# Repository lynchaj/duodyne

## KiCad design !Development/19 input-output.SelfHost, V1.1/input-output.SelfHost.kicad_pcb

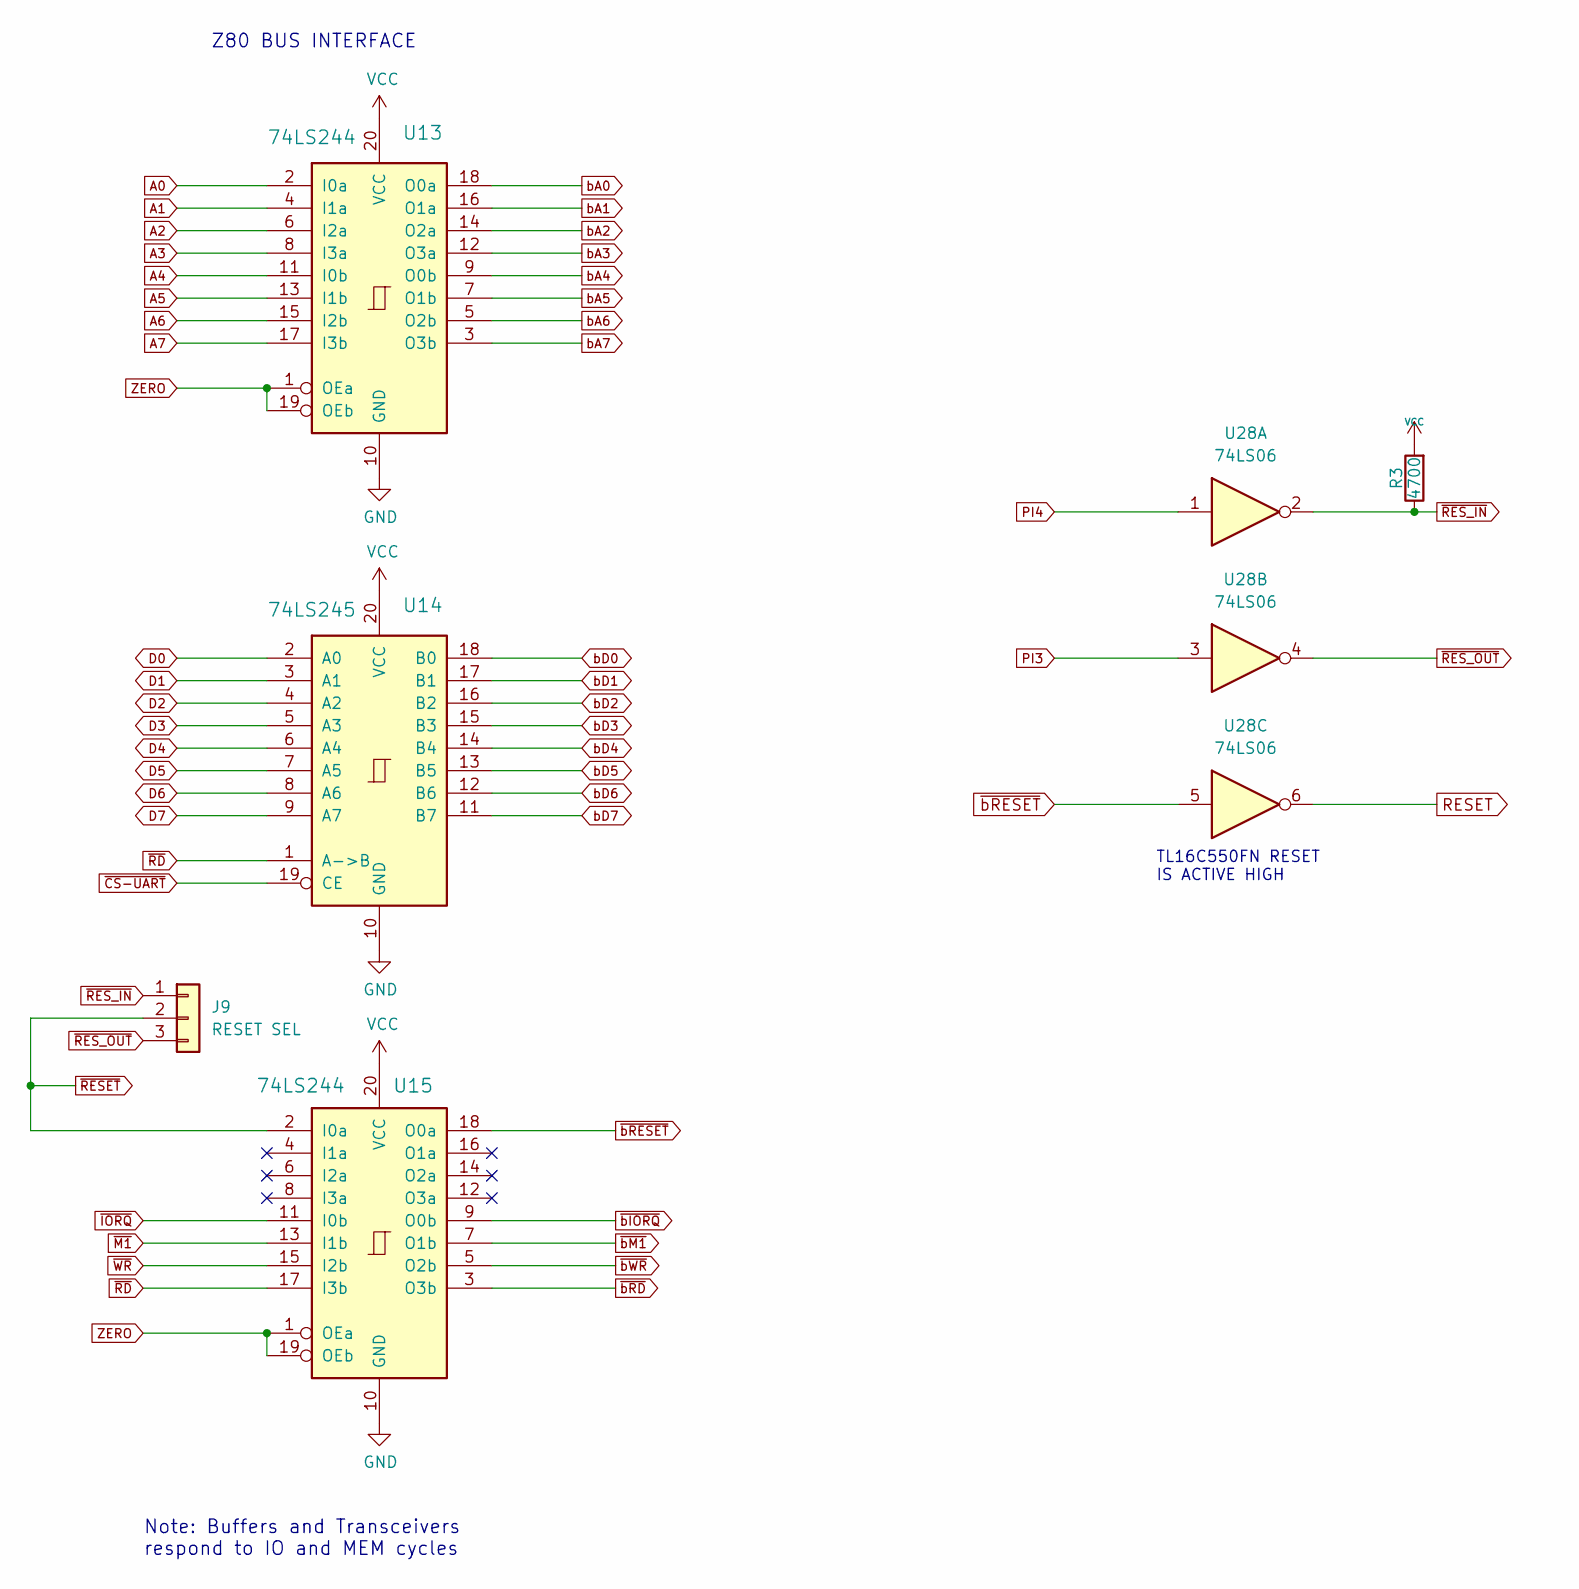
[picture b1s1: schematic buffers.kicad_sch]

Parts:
J9: RESET SEL; PinHeader_1x03_P2.54mm_Vertical
R3: 4700; R_Axial_DIN0207_L6.3mm_D2.5mm_P7.62mm_Horizontal
U13, U15: 74LS244; DIP-20_W7.62mm_Socket
U14: 74LS245; DIP-20_W7.62mm_Socket
U28: 74LS06

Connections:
A0: U13.2 (I0a); also elsewhere on the board
A1: U13.4 (I1a); also elsewhere on the board
A2: U13.6 (I2a); also elsewhere on the board
A5: U13.13 (I1b); also elsewhere on the board
A6: U13.15 (I2b); also elsewhere on the board
A7: U13.17 (I3b); also elsewhere on the board
D0: U14.2 (A0); also elsewhere on the board
D1: U14.3 (A1); also elsewhere on the board
D2: U14.4 (A2); also elsewhere on the board
D3: U14.5 (A3); also elsewhere on the board
D4: U14.6 (A4); also elsewhere on the board
D5: U14.7 (A5); also elsewhere on the board
D6: U14.8 (A6); also elsewhere on the board
D7: U14.9 (A7); also elsewhere on the board
PI3: U28.3; also elsewhere on the board
PI4: U28.1; also elsewhere on the board
RESET: U28.6; also elsewhere on the board
ZERO: U13.1 (OEa), U13.19 (OEb), U15.1 (OEa), U15.19 (OEb); also elsewhere on the board
bA0: U13.18 (O0a); also elsewhere on the board
bA1: U13.16 (O1a); also elsewhere on the board
bA2: U13.14 (O2a); also elsewhere on the board
bA4: U13.9 (O0b); also elsewhere on the board
bA5: U13.7 (O1b); also elsewhere on the board
bA6: U13.5 (O2b); also elsewhere on the board
bA7: U13.3 (O3b); also elsewhere on the board
bD0: U14.18 (B0); also elsewhere on the board
bD1: U14.17 (B1); also elsewhere on the board
bD2: U14.16 (B2); also elsewhere on the board
bD3: U14.15 (B3); also elsewhere on the board
bD4: U14.14 (B4); also elsewhere on the board
bD5: U14.13 (B5); also elsewhere on the board
bD6: U14.12 (B6); also elsewhere on the board
bD7: U14.11 (B7); also elsewhere on the board
~IORQ: U15.11 (I0b); also elsewhere on the board
~M1: U15.13 (I1b); also elsewhere on the board
~RD: U14.1 (A->B), U15.17 (I3b); also elsewhere on the board
~RESET: J9.2, U15.2 (I0a); also elsewhere on the board
~RES_IN: J9.1, R3.1, U28.2; also elsewhere on the board
~RES_OUT: J9.3, U28.4; also elsewhere on the board
~WR: U15.15 (I2b); also elsewhere on the board
~bIORQ: U15.9 (O0b); also elsewhere on the board
~bM1: U15.7 (O1b); also elsewhere on the board
~bRD: U15.3 (O3b); also elsewhere on the board
~bRESET: U15.18 (O0a), U28.5; also elsewhere on the board
~bWR: U15.5 (O2b); also elsewhere on the board

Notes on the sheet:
TL16C550FN RESET IS ACTIVE HIGH
Z80 BUS INTERFACE
Note: Buffers and Transceivers respond to IO and MEM cycles

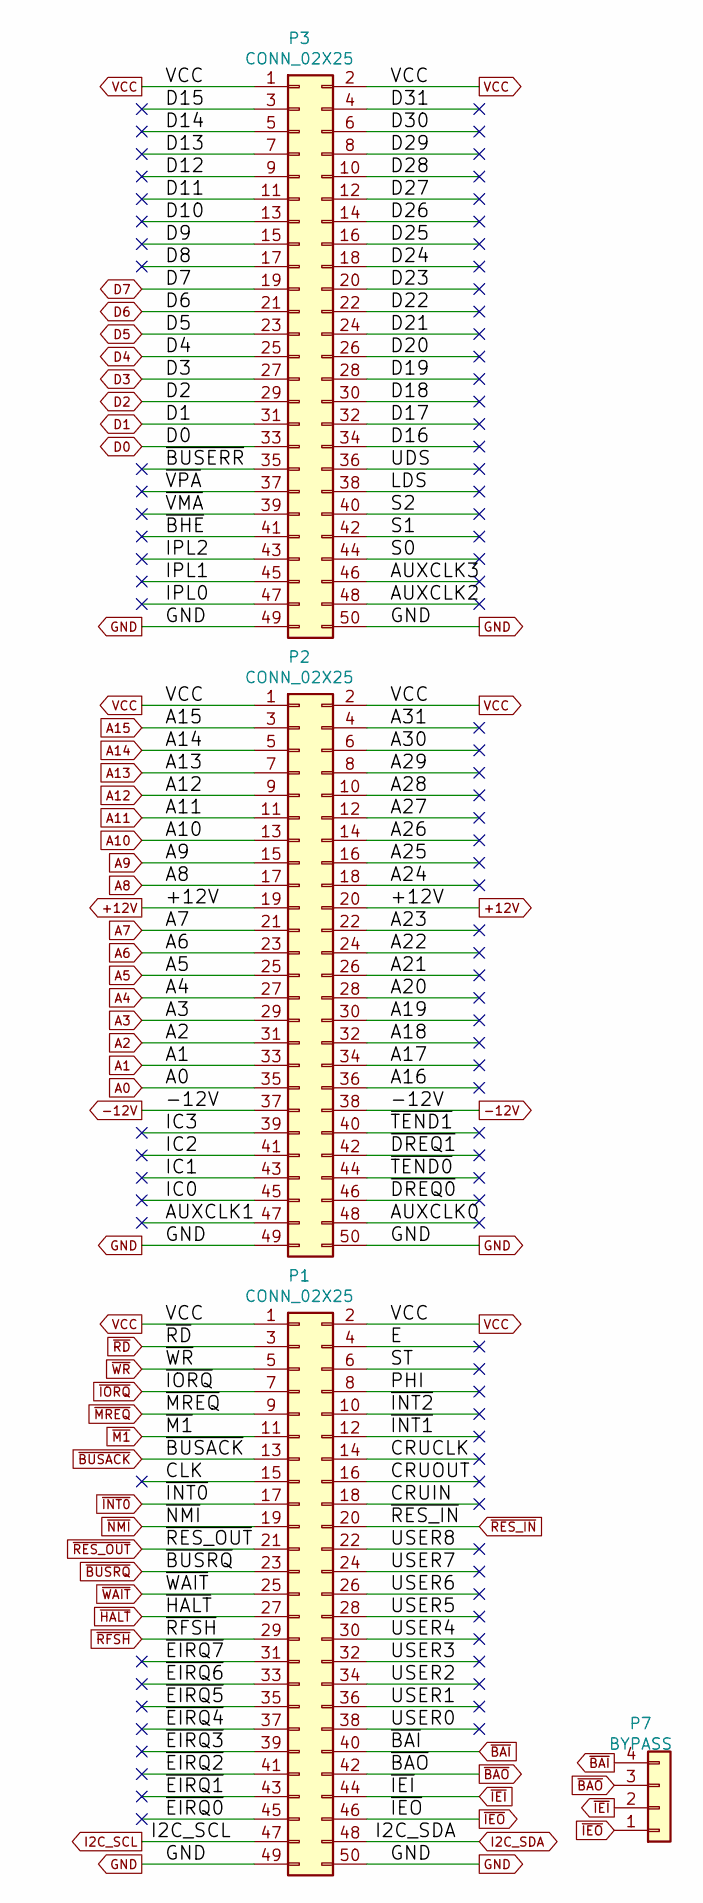
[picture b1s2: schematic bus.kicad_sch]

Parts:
P1, P2, P3: CONN_02X25; IDC-Header_2x25_P2.54mm_Horizontal
P7: BYPASS; PinHeader_1x04_P2.54mm_Vertical

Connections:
+12V: P2.19, P2.20
-12V: P2.37, P2.38
/bus/A16: P2.36
/bus/A17: P2.34
/bus/A18: P2.32
/bus/A19: P2.30
/bus/A20: P2.28
/bus/A21: P2.26
/bus/A22: P2.24
/bus/A23: P2.22
/bus/A24: P2.18
/bus/A25: P2.16
/bus/A26: P2.14
/bus/A27: P2.12
/bus/A28: P2.10
/bus/A29: P2.8
/bus/A30: P2.6
/bus/A31: P2.4
/bus/AUXCLK0: P2.48
/bus/AUXCLK1: P2.47
/bus/AUXCLK2: P3.48
/bus/AUXCLK3: P3.46
/bus/CLK: P1.15
/bus/CRUCLK: P1.14
/bus/CRUIN: P1.18
/bus/CRUOUT: P1.16
/bus/D8: P3.17
/bus/D9: P3.15
/bus/D10: P3.13
/bus/D11: P3.11
/bus/D12: P3.9
/bus/D13: P3.7
/bus/D14: P3.5
/bus/D15: P3.3
/bus/D16: P3.34
/bus/D17: P3.32
/bus/D18: P3.30
/bus/D19: P3.28
/bus/D20: P3.26
/bus/D21: P3.24
/bus/D22: P3.22
/bus/D23: P3.20
/bus/D24: P3.18
/bus/D25: P3.16
/bus/D26: P3.14
/bus/D27: P3.12
/bus/D28: P3.10
/bus/D29: P3.8
/bus/D30: P3.6
/bus/D31: P3.4
/bus/E: P1.4
/bus/IC0: P2.45
/bus/IC1: P2.43
/bus/IC2: P2.41
/bus/IC3: P2.39
/bus/IPL0: P3.47
/bus/IPL1: P3.45
/bus/IPL2: P3.43
/bus/LDS: P3.38
/bus/PHI: P1.8
/bus/S0: P3.44
/bus/S1: P3.42
/bus/S2: P3.40
/bus/ST: P1.6
/bus/UDS: P3.36
/bus/USER0: P1.38
/bus/USER1: P1.36
/bus/USER2: P1.34
/bus/USER3: P1.32
/bus/USER4: P1.30
/bus/USER5: P1.28
/bus/USER6: P1.26
/bus/USER7: P1.24
/bus/USER8: P1.22
/bus/~BHE: P3.41
/bus/~BUSERR: P3.35
/bus/~DREQ0: P2.46
/bus/~DREQ1: P2.42
/bus/~EIRQ0: P1.45
/bus/~EIRQ1: P1.43
/bus/~EIRQ2: P1.41
/bus/~EIRQ3: P1.39
/bus/~EIRQ4: P1.37
/bus/~EIRQ5: P1.35
/bus/~EIRQ6: P1.33
/bus/~EIRQ7: P1.31
/bus/~INT1: P1.12
/bus/~INT2: P1.10
/bus/~TEND0: P2.44
/bus/~TEND1: P2.40
/bus/~VMA: P3.39
/bus/~VPA: P3.37
A0: P2.35; also elsewhere on the board
A1: P2.33; also elsewhere on the board
A2: P2.31; also elsewhere on the board
A5: P2.25; also elsewhere on the board
A6: P2.23; also elsewhere on the board
A7: P2.21; also elsewhere on the board
A8: P2.17; also elsewhere on the board
A9: P2.15; also elsewhere on the board
A10: P2.13; also elsewhere on the board
A11: P2.11; also elsewhere on the board
A12: P2.9; also elsewhere on the board
A13: P2.7; also elsewhere on the board
A14: P2.5; also elsewhere on the board
A15: P2.3; also elsewhere on the board
D0: P3.33; also elsewhere on the board
D1: P3.31; also elsewhere on the board
D2: P3.29; also elsewhere on the board
D3: P3.27; also elsewhere on the board
D4: P3.25; also elsewhere on the board
D5: P3.23; also elsewhere on the board
D6: P3.21; also elsewhere on the board
D7: P3.19; also elsewhere on the board
I2C_SCL: P1.47; also elsewhere on the board
I2C_SDA: P1.48; also elsewhere on the board
~BAI: P1.40, P7.4
~BAO: P1.42, P7.3
~BUSACK: P1.13; also elsewhere on the board
~HALT: P1.27; also elsewhere on the board
~IEO: P1.46, P7.1; also elsewhere on the board
~INT0: P1.17; also elsewhere on the board
~IORQ: P1.7; also elsewhere on the board
~M1: P1.11; also elsewhere on the board
~MREQ: P1.9; also elsewhere on the board
~NMI: P1.19; also elsewhere on the board
~RD: P1.3; also elsewhere on the board
~RES_IN: P1.20; also elsewhere on the board
~RES_OUT: P1.21; also elsewhere on the board
~RFSH: P1.29; also elsewhere on the board
~WAIT: P1.25; also elsewhere on the board
~WR: P1.5; also elsewhere on the board

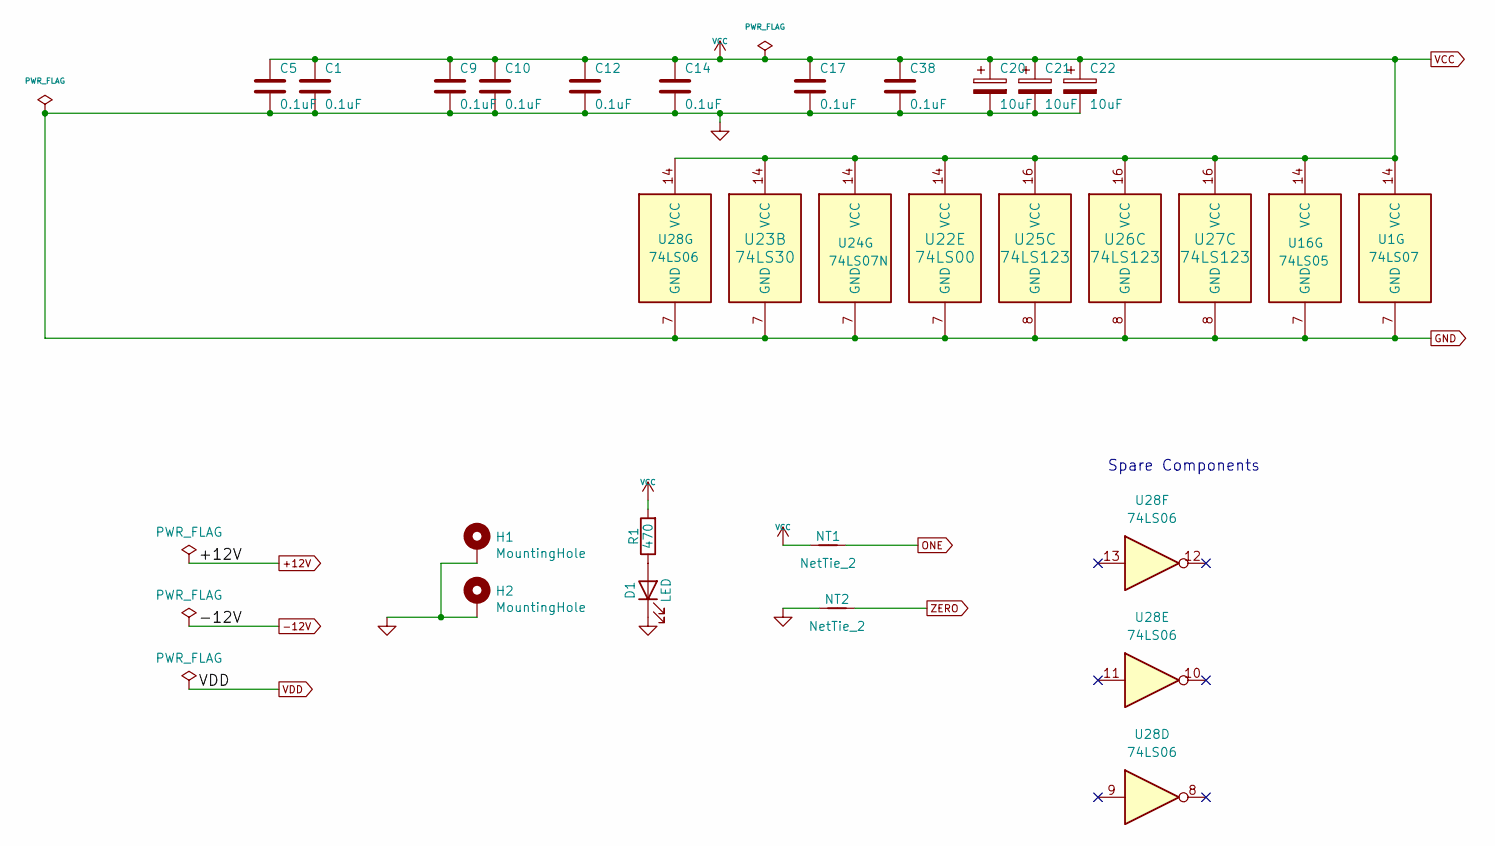
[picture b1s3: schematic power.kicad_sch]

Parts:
C1, C5, C9, C10, C12, C14, C17, C38: 0.1uF; C_Disc_D5.0mm_W2.5mm_P5.00mm
C20, C21, C22: 10uF; CP_Radial_D5.0mm_P2.50mm
D1: LED; LED_D3.0mm_Horizontal_O3.81mm_Z2.0mm
H1, H2: MountingHole; MountingHole_3.2mm_M3_Pad
NT1, NT2: NetTie_2; NetTie-2_THT_Pad0.3mm
R1: 470; R_Axial_DIN0207_L6.3mm_D2.5mm_P7.62mm_Horizontal
U1: 74LS07; DIP-14_W7.62mm_Socket
U16: 74LS05; DIP-14_W7.62mm_Socket
U22: 74LS00; DIP-14_W7.62mm_Socket
U23: 74LS30; DIP-14_W7.62mm_Socket
U24: 74LS07N; DIP-14_W7.62mm_Socket
U25, U26, U27: 74LS123; DIP-16_W7.62mm_Socket
U28: 74LS06

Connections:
unnamed: D1.2 (A), R1.1
ONE: NT1.2; also elsewhere on the board
ZERO: NT2.2; also elsewhere on the board

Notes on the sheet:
Spare Components

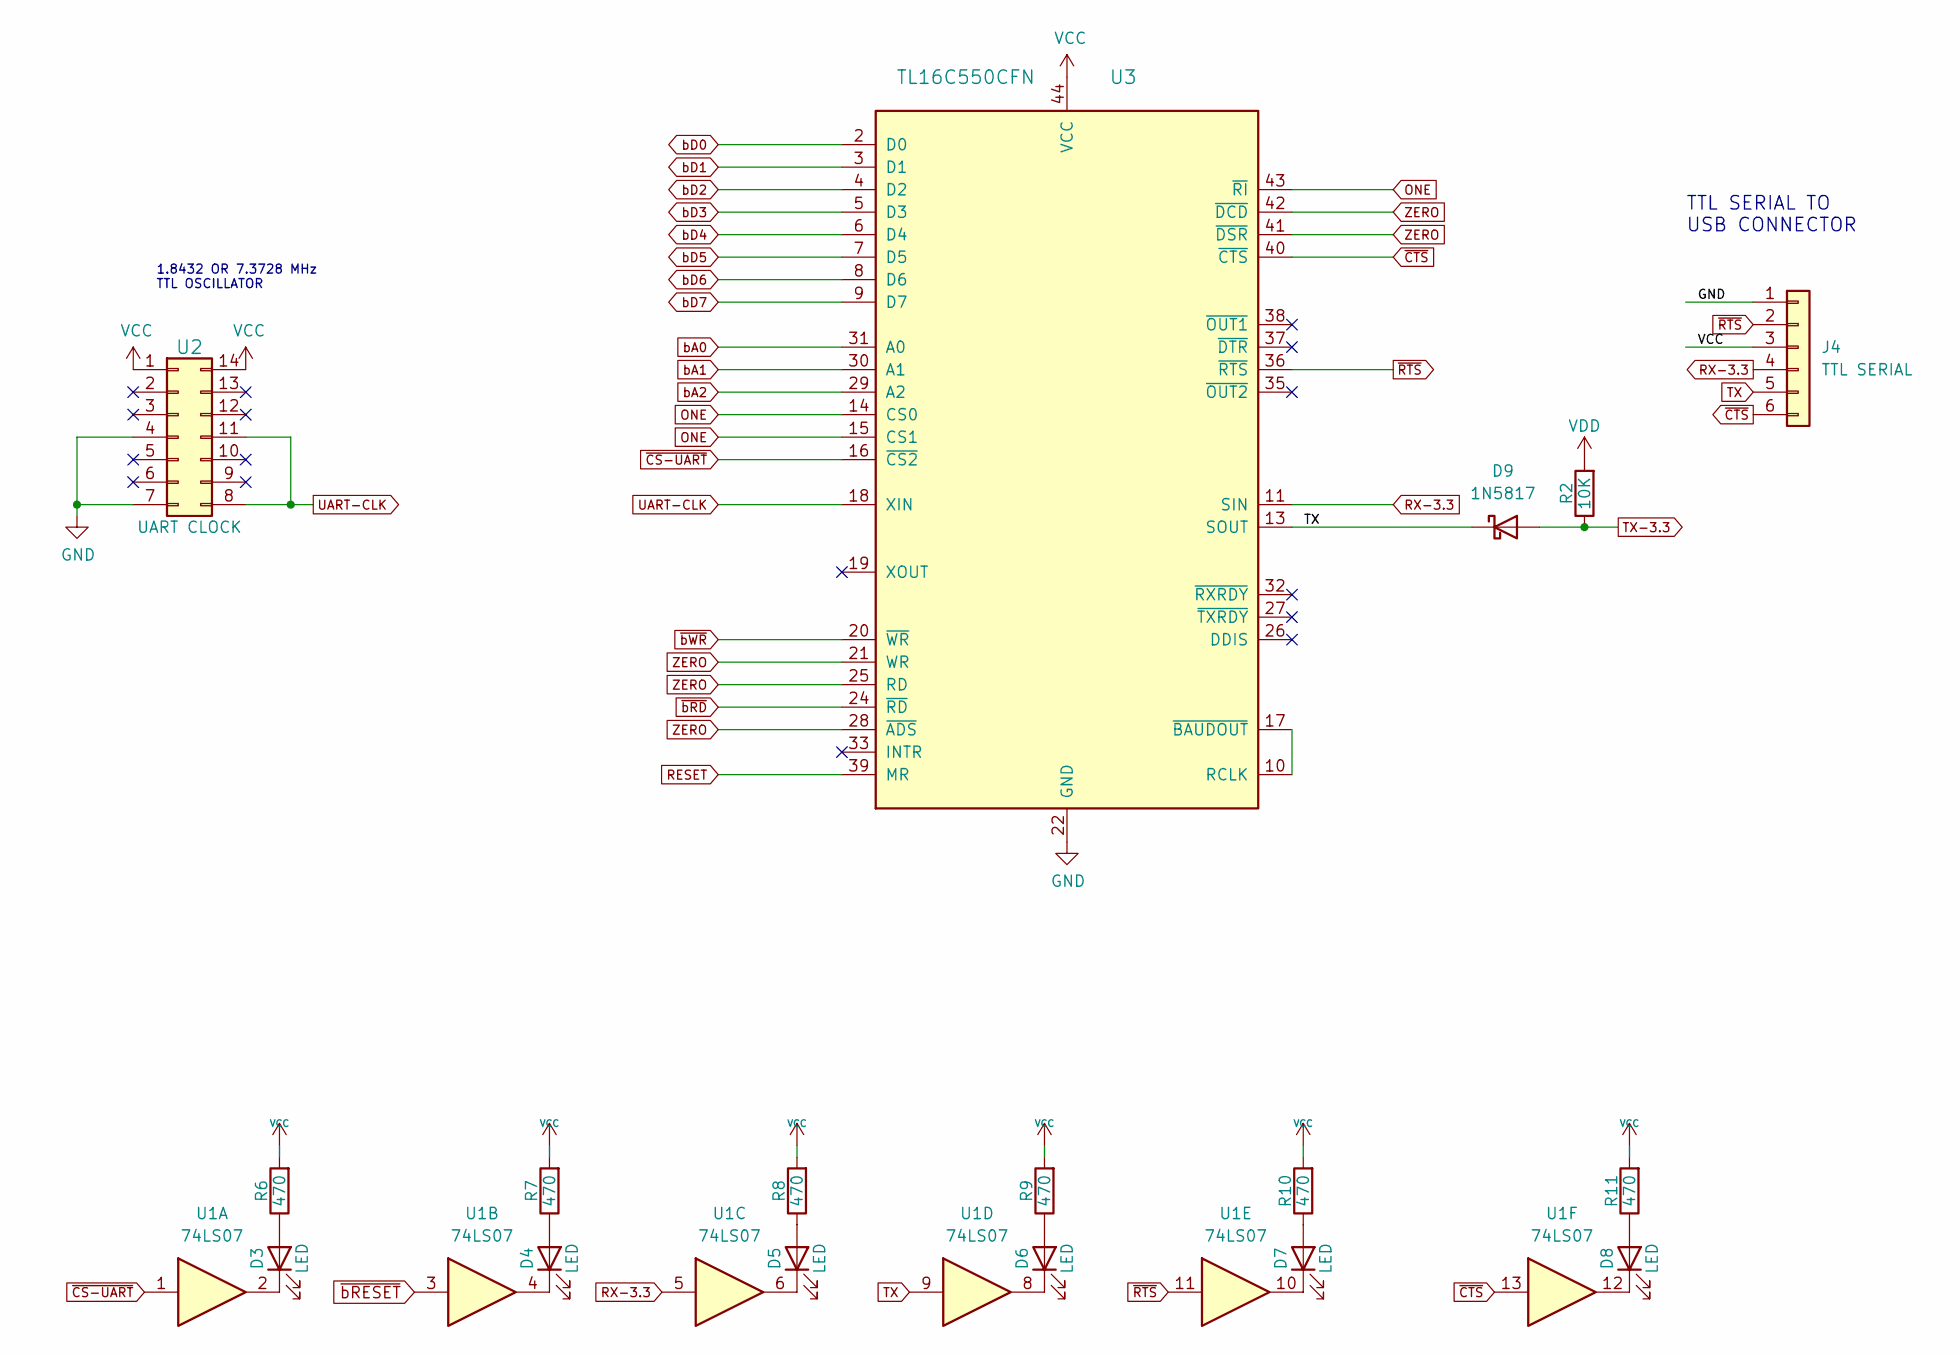
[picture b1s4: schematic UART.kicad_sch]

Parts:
D3, D4, D5, D6, D7, D8: LED; LED_D3.0mm_Horizontal_O3.81mm_Z2.0mm
D9: 1N5817; D_DO-41_SOD81_P10.16mm_Horizontal
J4: TTL SERIAL; PinHeader_1x06_P2.54mm_Horizontal
R2: 10K; R_Axial_DIN0207_L6.3mm_D2.5mm_P7.62mm_Horizontal
R6, R7, R8, R9, R10, R11: 470; R_Axial_DIN0207_L6.3mm_D2.5mm_P7.62mm_Horizontal
U1: 74LS07; DIP-14_W7.62mm_Socket
U2: UART CLOCK; DIP-14_W7.62mm_Socket
U3: TL16C550CFN; PLCC-44_THT-Socket

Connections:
unnamed: D6.1 (K), U1.8
unnamed: D6.2 (A), R9.1
unnamed: D7.1 (K), U1.10
unnamed: D7.2 (A), R10.1
unnamed: D8.1 (K), U1.12
unnamed: D8.2 (A), R11.1
unnamed: U3.10 (RCLK), U3.17 (~BAUDOUT)
ONE: U3.14 (CS0), U3.15 (CS1), U3.43 (~RI); also elsewhere on the board
RESET: U3.39 (MR); also elsewhere on the board
RX-3.3: J4.4, U1.5, U3.11 (SIN); also elsewhere on the board
TX: D9.1 (K), J4.5, U1.9, U3.13 (SOUT)
TX-3.3: D9.2 (A), R2.1; also elsewhere on the board
UART-CLK: U2.8, U2.11, U3.18 (XIN)
VDD: R2.2; also elsewhere on the board
ZERO: U3.21 (WR), U3.25 (RD), U3.28 (~ADS), U3.41 (~DSR), U3.42 (~DCD); also elsewhere on the board
bA0: U3.31 (A0); also elsewhere on the board
bA1: U3.30 (A1); also elsewhere on the board
bA2: U3.29 (A2); also elsewhere on the board
bD0: U3.2 (D0); also elsewhere on the board
bD1: U3.3 (D1); also elsewhere on the board
bD2: U3.4 (D2); also elsewhere on the board
bD3: U3.5 (D3); also elsewhere on the board
bD4: U3.6 (D4); also elsewhere on the board
bD5: U3.7 (D5); also elsewhere on the board
bD6: U3.8 (D6); also elsewhere on the board
bD7: U3.9 (D7); also elsewhere on the board
~CTS: J4.6, U1.13, U3.40 (~CTS)
~RTS: J4.2, U1.11, U3.36 (~RTS)
~bRD: U3.24 (~RD); also elsewhere on the board
~bRESET: U1.3; also elsewhere on the board
~bWR: U3.20 (~WR); also elsewhere on the board

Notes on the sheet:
TTL SERIAL TO USB CONNECTOR
1.8432 OR 7.3728 MHz TTL OSCILLATOR

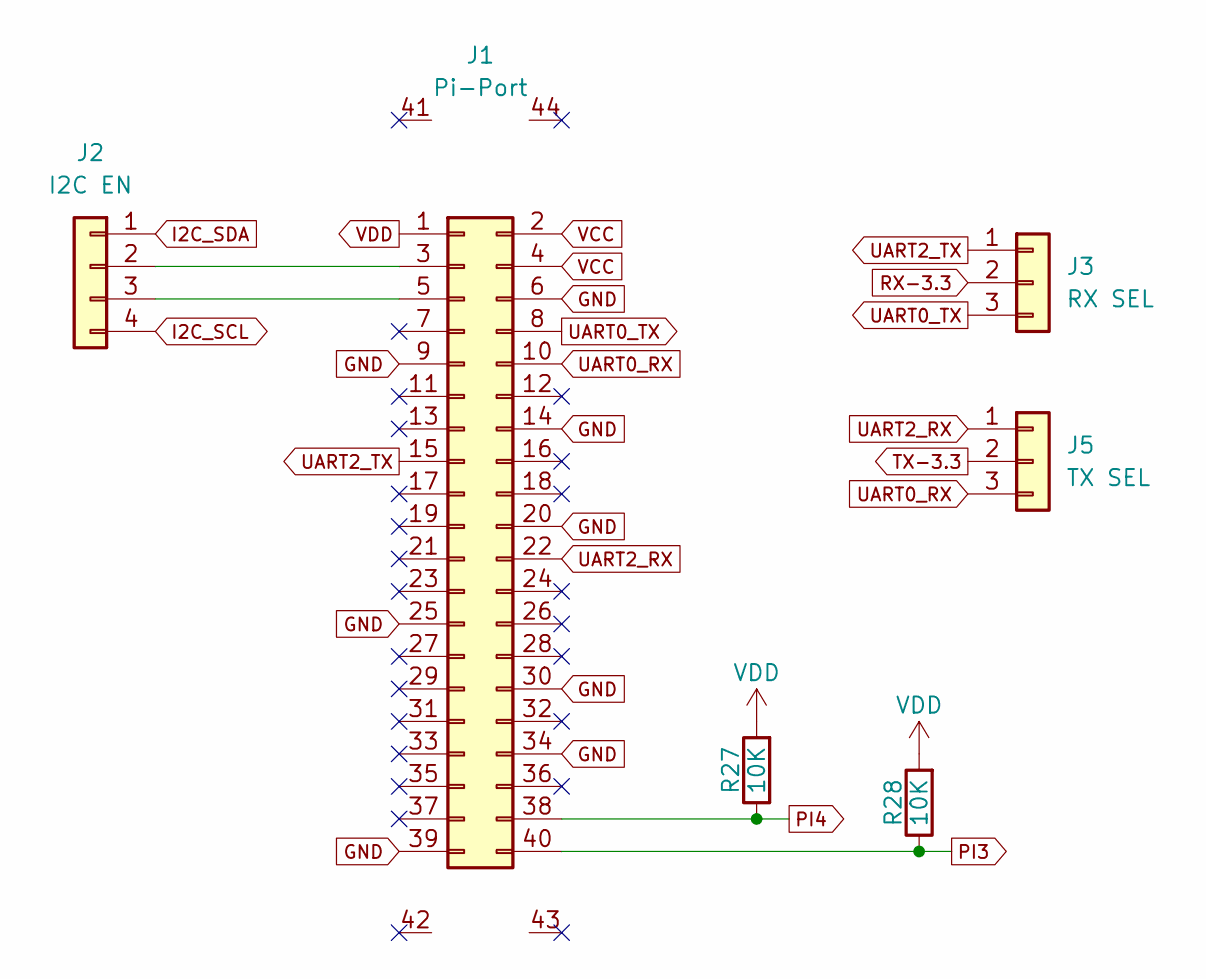
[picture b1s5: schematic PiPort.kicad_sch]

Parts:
J1: Pi-Port
J2: I2C EN; PinHeader_1x04_P2.54mm_Vertical
J3: RX SEL; PinHeader_1x03_P2.54mm_Vertical
J5: TX SEL; PinHeader_1x03_P2.54mm_Vertical
R27, R28: 10K; R_Axial_DIN0207_L6.3mm_D2.5mm_P7.62mm_Horizontal

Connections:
I2C_SCL: J2.4; also elsewhere on the board
I2C_SDA: J2.1; also elsewhere on the board
unnamed: J1.3, J2.2
unnamed: J1.5, J2.3
PI3: J1.40, R28.1; also elsewhere on the board
PI4: J1.38, R27.1; also elsewhere on the board
RX-3.3: J3.2; also elsewhere on the board
TX-3.3: J5.2; also elsewhere on the board
UART0_RX: J1.10, J5.3
UART0_TX: J1.8, J3.3
UART2_RX: J1.22, J5.1
UART2_TX: J1.15, J3.1
VDD: J1.1, R27.2, R28.2; also elsewhere on the board
